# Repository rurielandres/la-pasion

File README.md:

Proyecto Minisumo - AD VICTORIAM

## 👥 Autores
- **Uriel Ramirez**   
- **Demian Ramirez** 
  
---

## 📖 Introducción#
El proyecto consiste en un robot minisumo autónomo que emplea distintos sensores para orientarse dentro del área de combate.  
- **Sensor frontal**: impulsa al robot hacia adelante para atacar.  
- **Sensores laterales**: permiten reorientarse frente a obstáculos o rivales.  
- **Sensor de piso**: asegura que el robot permanezca dentro de la arena de enfrentamiento.  

En conjunto, se trata de un mecanismo sencillo pero eficaz para la competencia de minisumo.

---

## ⚙️ Esquema en bloques
- Batería
- Sensor lateral
- Microcontrolador (ESP32 C3 mini)
- Sensor frontal
- Sensor de piso
- DRV8833 (Puente H)
- Motores

---

## 💰 Componentes y costos aproximados
| Componente                   | Costo (ARS) |
|------------------------------|-------------|
| ESP32 C3 super mini          | 10.000      |
| Batería de Lipo              | 30.040      |
| TCRT5000 (sensor )    | 3.700       |
| AD-32 (sensor) x2      | 2.300       |
| Motores Pololu 250RPM   x2     | 9.800       |
| DRV8833 (puente H)           | 4.000       |
| Carrocería                   | 11.000      |
| hc sr04                    | 3.500  |
| **Total**                    | **76.640**  |

---

## 🎯 Objetivo del Proyecto

El objetivo del robot minisumo *La Passione* es participar en competencias de sumo robótico, 
donde debe detectar, atacar y desplazar a su oponente fuera del área de combate (tatami).  
Para lograrlo, combina distintos sensores y un sistema de control basado en el ESP32 S3:

- **Atacar directamente** cuando el sensor frontal detecta un rival.  
- **Reorientarse** mediante los sensores laterales para enfrentar al oponente de manera estratégica.  
- **Mantenerse dentro del área de combate** gracias al sensor de piso que evita salidas accidentales.

 ---  
 
## 📐Diseño

## Esquematico

## PCB

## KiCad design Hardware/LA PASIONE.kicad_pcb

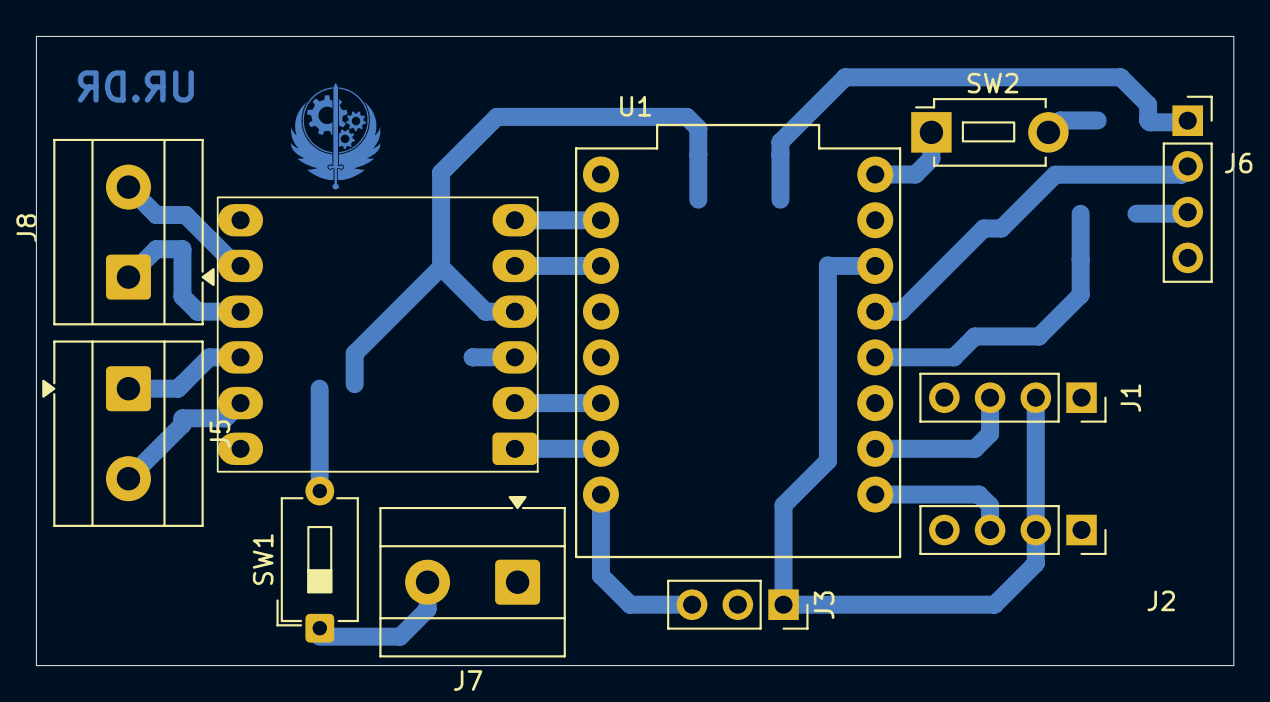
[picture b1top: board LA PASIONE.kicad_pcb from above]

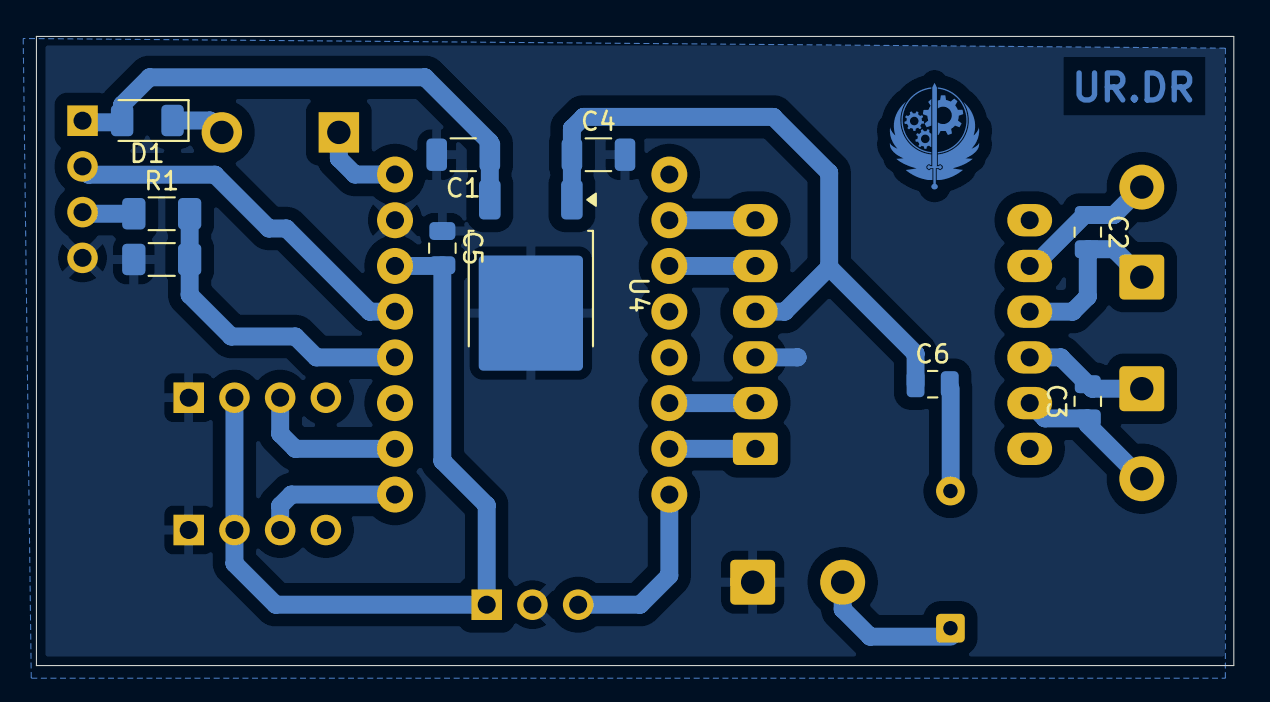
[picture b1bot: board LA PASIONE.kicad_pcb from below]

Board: 2 copper layers, 66.5 x 34.9 mm, 21 parts (10 on the bottom side), 21 nets.

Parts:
C1, C4: 10uF; C_1206_3216Metric
C2, C3, C5, C6: 100nF; C_0805_2012Metric
D1: 1n4007; D_1206_3216Metric
J1, J2, J6: Conn_01x04; PinSocket_1x04_P2.54mm_Vertical
J3: Conn_01x03; PinSocket_1x03_P2.54mm_Vertical
J5, J7, J8: Screw_Terminal_01x02; TerminalBlock_MetzConnect_Type055_RT01502HDWU_1x02_P5.00mm_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
R1: 1K; R_1206_3216Metric_Pad1.30x1.75mm_HandSolder
R2: 2K; R_1206_3216Metric_Pad1.30x1.75mm_HandSolder
SW1: SW_SPST; SW_DIP_SPSTx01_Slide_6.7x4.1mm_W7.62mm_P2.54mm_LowProfile
SW2: SW_Push; SW_PUSH_1P1T_6x3.5mm_H4.3_APEM_MJTP1243
U1: MODULE_ESP32-C3_SUPERMINI
U2: DRV8833
U4: L7805; TO-252-2

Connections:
+3.3V: C5.2, J1.2, J2.2, J3.1, U1.11 (3V3)
+5V: C1.1, D1.2 (A), J6.1, U4.3 (OUT)
/IN1: U1.2 (GPIO6), U2.6 (IN1)
/IN2: U1.3 (GPIO7), U2.5 (IN2)
/IN3: U1.6 (GPIO10), U2.2 (IN3)
/IN4: U1.7 (GPIO20), U2.1 (IN4)
/M1: C3.1, J5.2, U2.11 (OUT4)
/M2: C3.2, J5.1, U2.10 (OUT3)
/M3: C2.2, J8.1, U2.9 (OUT2)
/M4: C2.1, J8.2, U2.8 (OUT1)
/OutPut3: J2.3, U1.16 (GPIO0)
/OutPut4: J3.3, U1.8 (GPIO21)
/Output1: R1.2, R2.2, U1.13 (GPIO3)
/Output2: J1.3, U1.15 (GPIO1)
/TRIGGER: J6.2, U1.12 (GPIO4)
GND: C1.2, C4.2, C5.1, J1.1, J2.1, J3.2, J6.4, J7.1, R2.1, U1.10 (GND), U2.3 (GND), U4.2 (GND)
unnamed: D1.1 (K), SW2.2
unnamed: J6.3, R1.1
unnamed: J7.2, SW1.1 (A)
unnamed: SW2.1, U1.9 (5V)
VCC: C4.1, C6.1, SW1.2 (B), U2.4 (VCC), U4.1 (IN)

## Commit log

2026-04-15 README.md
2026-04-22 Create Código (incompleto)
2026-04-29 Update Código (incompleto)
2026-05-06 Rename Fabulous Snicket-Trug.stl to Fabulous Snicket-Trug(desactualizado y corrompido)).stl
2026-06-11 Rename diseño 3d/Fabulous Snicket-Trug (3).stl to (NO SIRVE)
2026-06-11 Delete_3d
2026-06-23 Create Hardware
